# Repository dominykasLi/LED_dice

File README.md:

# LED_dice
Simple, random 6 sided dice generation electronics project.

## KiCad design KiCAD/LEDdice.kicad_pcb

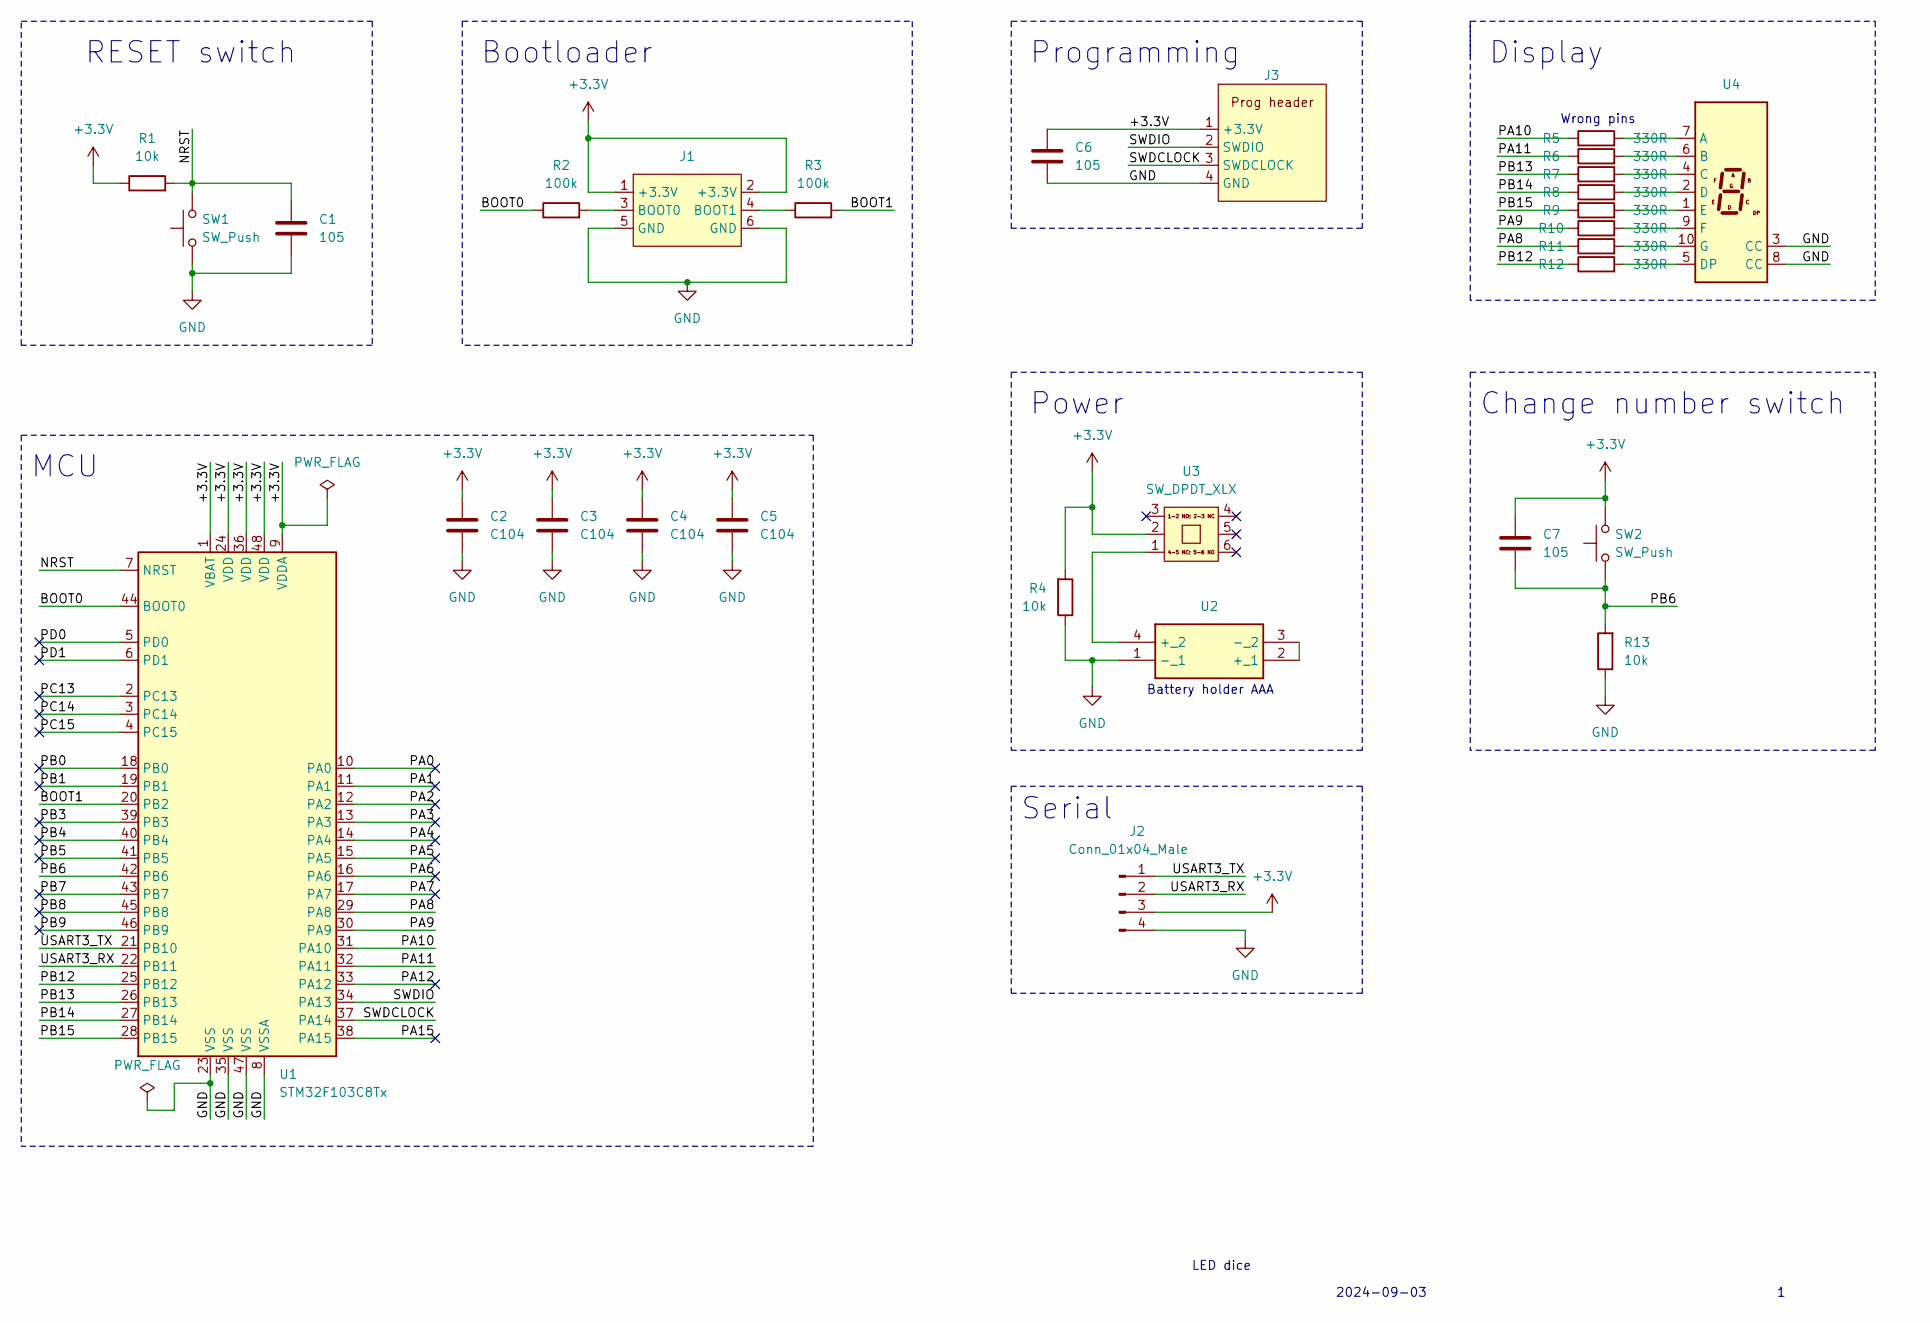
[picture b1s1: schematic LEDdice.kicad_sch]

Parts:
C1, C6, C7: 105; C_0805_2012Metric
C2, C3, C4, C5: C104; C_0805_2012Metric
J1: STM32_BOOT_Header_2x3; PinHeader_2x03_P2.54mm_Vertical
J2: Conn_01x04_Male; PinHeader_1x04_P2.54mm_Vertical
J3: STM32_Programming_Header_4; PinHeader_1x04_P2.54mm_Vertical
R1, R4, R13: 10k; R_0805_2012Metric
R2, R3: 100k; R_0805_2012Metric
R5, R6, R7, R8, R9, R10, R11, R12: 330R; R_0805_2012Metric
SW1: SW_Push; SW_Push_1P1T_NO_6x6mm_H9.5mm
SW2: SW_Push; SW_PUSH-12mm
U1: STM32F103C8Tx; LQFP-48_7x7mm_P0.5mm
U2: 1023; 2xAAA_Battery_Holder_SMD
U3: SW_DPDT_XLX
U4: 7_seg_5161AS_CC; 7_Seg_5161AS

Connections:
+3.3V: C2.1, C3.1, C4.1, C5.1, C6.1, C7.1, J1.1 (+3.3V), J1.2 (+3.3V), J2.3, J3.1 (+3.3V), R1.1, R4.2, SW2.2, U1.1 (VBAT), U1.9 (VDDA), U1.24 (VDD), U1.36 (VDD), U1.48 (VDD), U3.2; also elsewhere on the board
/BOOT0: R2.1, U1.44 (BOOT0)
/BOOT1: R3.2, U1.20 (PB2)
/NRST: C1.1, R1.2, SW1.2, U1.7 (NRST); also elsewhere on the board
/PA0: U1.10 (PA0)
/PA1: U1.11 (PA1)
/PA2: U1.12 (PA2)
/PA3: U1.13 (PA3)
/PA4: U1.14 (PA4)
/PA5: U1.15 (PA5)
/PA6: U1.16 (PA6)
/PA7: U1.17 (PA7)
/PA8: R11.1, U1.29 (PA8)
/PA9: R10.1, U1.30 (PA9)
/PA10: R5.1, U1.31 (PA10)
/PA11: R6.1, U1.32 (PA11)
/PA12: U1.33 (PA12)
/PA15: U1.38 (PA15)
/PB0: U1.18 (PB0)
/PB1: U1.19 (PB1)
/PB3: U1.39 (PB3)
/PB4: U1.40 (PB4)
/PB5: U1.41 (PB5)
/PB6: C7.2, R13.2, SW2.1, U1.42 (PB6); also elsewhere on the board
/PB7: U1.43 (PB7)
/PB8: U1.45 (PB8)
/PB9: U1.46 (PB9)
/PB12: R12.1, U1.25 (PB12)
/PB13: R7.1, U1.26 (PB13)
/PB14: R8.1, U1.27 (PB14)
/PB15: R9.1, U1.28 (PB15)
/PC13: U1.2 (PC13)
/PC14: U1.3 (PC14)
/PC15: U1.4 (PC15)
/PD0: U1.5 (PD0)
/PD1: U1.6 (PD1)
/SWDCLOCK: J3.3 (SWDCLOCK), U1.37 (PA14)
/SWDIO: J3.2 (SWDIO), U1.34 (PA13)
/USART3_RX: J2.2, U1.22 (PB11)
/USART3_TX: J2.1, U1.21 (PB10)
GND: C1.2, C2.2, C3.2, C4.2, C5.2, C6.2, J1.5 (GND), J1.6 (GND), J2.4, J3.4 (GND), R4.1, R13.1, SW1.1, U1.8 (VSSA), U1.23 (VSS), U1.35 (VSS), U1.47 (VSS), U2.1 (-_1), U4.3 (CC), U4.8 (CC); also elsewhere on the board
unnamed: J1.3 (BOOT0), R2.2
unnamed: J1.4 (BOOT1), R3.1
unnamed: R5.2, U4.7 (A)
unnamed: R6.2, U4.6 (B)
unnamed: R7.2, U4.4 (C)
unnamed: R8.2, U4.2 (D)
unnamed: R9.2, U4.1 (E)
unnamed: R10.2, U4.9 (F)
unnamed: R11.2, U4.10 (G)
unnamed: R12.2, U4.5 (DP)
unnamed: U2.2 (+_1), U2.3 (-_2)
unnamed: U2.4 (+_2), U3.1

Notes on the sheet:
Bootloader
Programming
RESET switch
Display
LED dice
Serial
MCU
2024-09-03
Change number switch
Wrong pins
Battery holder AAA
Power

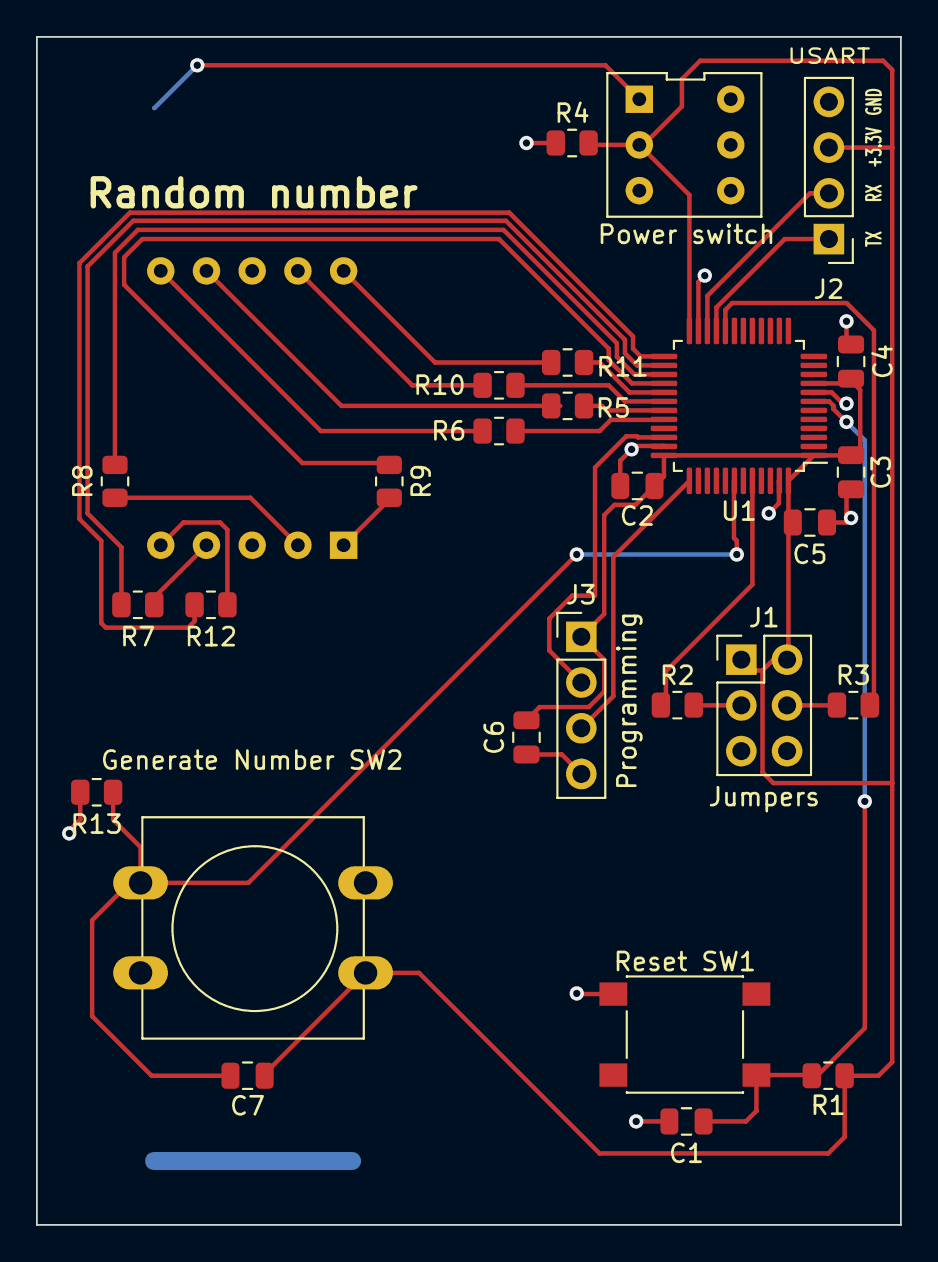
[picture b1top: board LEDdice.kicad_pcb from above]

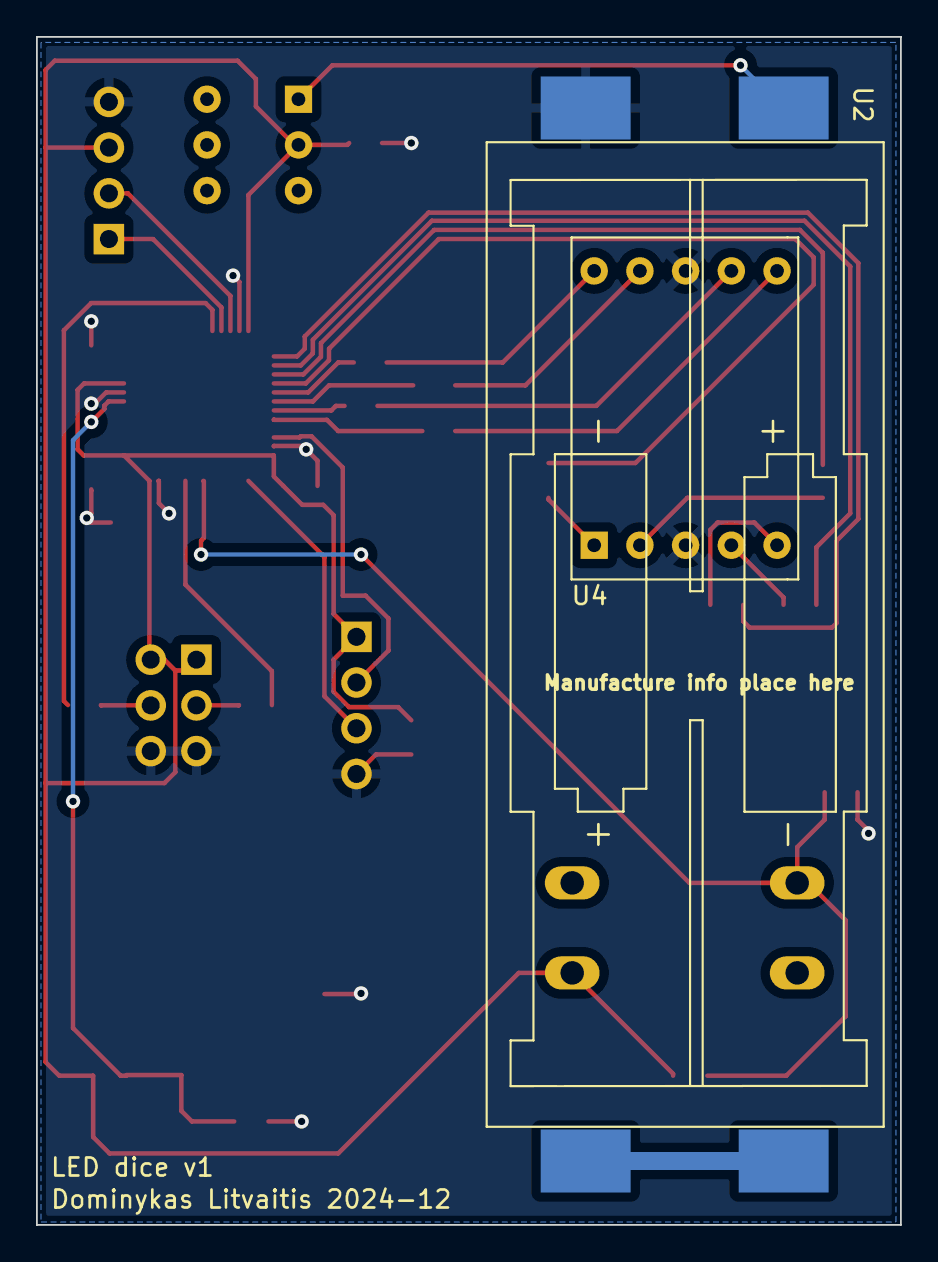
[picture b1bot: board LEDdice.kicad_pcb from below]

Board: 2 copper layers, 48.0 x 66.0 mm, 29 parts (2 on the bottom side), 30 nets.

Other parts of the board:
Generate Number SW2: SW_Push; SW_PUSH-12mm
Reset SW1: SW_Push; SW_Push_1P1T_NO_6x6mm_H9.5mm

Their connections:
+3.3V: Generate Number SW2.2; also elsewhere on the board
/NRST: Reset SW1.2; also elsewhere on the board
/PB6: Generate Number SW2.1; also elsewhere on the board
GND: Reset SW1.1; also elsewhere on the board

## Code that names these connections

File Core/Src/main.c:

/* USER CODE BEGIN Header */
/**
  ******************************************************************************
  * @file           : main.c
  * @brief          : Main program body
  ******************************************************************************
  * @attention
  *
  * Copyright (c) 2024 STMicroelectronics.
  * All rights reserved.
  *
  * This software is licensed under terms that can be found in the LICENSE file
  * in the root directory of this software component.
  * If no LICENSE file comes with this software, it is provided AS-IS.
  *
  ******************************************************************************
  */
/* USER CODE END Header */
/* Includes ------------------------------------------------------------------*/
#include "main.h"

/* Private includes ----------------------------------------------------------*/
/* USER CODE BEGIN Includes */
#include <time.h>
#include <stdlib.h>
#include <7seg.h>
/* USER CODE END Includes */

/* Private typedef -----------------------------------------------------------*/
/* USER CODE BEGIN PTD */

/* USER CODE END PTD */

/* Private define ------------------------------------------------------------*/
/* USER CODE BEGIN PD */

/* USER CODE END PD */

/* Private macro -------------------------------------------------------------*/
/* USER CODE BEGIN PM */

/* USER CODE END PM */

/* Private variables ---------------------------------------------------------*/
ADC_HandleTypeDef hadc1;

/* USER CODE BEGIN PV */

/* USER CODE END PV */

/* Private function prototypes -----------------------------------------------*/
void SystemClock_Config(void);
static void MX_GPIO_Init(void);
static void MX_ADC1_Init(void);
/* USER CODE BEGIN PFP */
void SystemClock_Config(void);
static void MX_GPIO_Init(void);
/* USER CODE END PFP */

/* Private user code ---------------------------------------------------------*/
/* USER CODE BEGIN 0 */

/* USER CODE END 0 */

/**
  * @brief  The application entry point.
  * @retval int
  */
int main(void)
{

  /* USER CODE BEGIN 1 */
  /* Random number to be generated between 1-6*/
  int Random_Number = 0;
  /* ADC raw values for rand() seed*/
  int raw = 0;
  /* USER CODE END 1 */

  /* MCU Configuration--------------------------------------------------------*/

  /* Reset of all peripherals, Initializes the Flash interface and the Systick. */
  HAL_Init();

  /* USER CODE BEGIN Init */

  /* USER CODE END Init */

  /* Configure the system clock */
  SystemClock_Config();

  /* USER CODE BEGIN SysInit */

  /* USER CODE END SysInit */

  /* Initialize all configured peripherals */
  MX_GPIO_Init();
  MX_ADC1_Init();
  /* USER CODE BEGIN 2 */

  /*This piece of code reads a tri-state pin and sets a random seed*/
  HAL_ADC_Start(&hadc1);
  HAL_ADC_PollForConversion(&hadc1, HAL_MAX_DELAY);
  raw = HAL_ADC_GetValue(&hadc1);
  srand(raw);
  /* USER CODE END 2 */

  /* Infinite loop */
  /* USER CODE BEGIN WHILE */
  while (1)
  {
    /* USER CODE END WHILE */

    /* USER CODE BEGIN 3 */

    // IF Button Is Pressed, get a random value
      if(HAL_GPIO_ReadPin(GPIOB, GPIO_PIN_6))
      {
          Clear_Display_Animation();
          /* random int between 1 and 6 */
          Random_Number = (rand() % 6) + 1;
          Display_Number(Random_Number);
          HAL_GPIO_WritePin(GPIOC, GPIO_PIN_13, GPIO_PIN_RESET);
          HAL_Delay(500);
      }
      else
      {
          // Else .. Turn LED OFF!
          // HAL_GPIO_WritePin(GPIOB, GPIO_PIN_15, GPIO_PIN_RESET);
      }
      
  }
  /* USER CODE END 3 */
}

/**
  * @brief System Clock Configuration
  * @retval None
  */
void SystemClock_Config(void)
{
  RCC_OscInitTypeDef RCC_OscInitStruct = {0};
  RCC_ClkInitTypeDef RCC_ClkInitStruct = {0};
  RCC_PeriphCLKInitTypeDef PeriphClkInit = {0};

  /** Initializes the RCC Oscillators according to the specified parameters
  * in the RCC_OscInitTypeDef structure.
  */
  RCC_OscInitStruct.OscillatorType = RCC_OSCILLATORTYPE_HSI;
  RCC_OscInitStruct.HSIState = RCC_HSI_ON;
  RCC_OscInitStruct.HSICalibrationValue = RCC_HSICALIBRATION_DEFAULT;
  RCC_OscInitStruct.PLL.PLLState = RCC_PLL_NONE;
  if (HAL_RCC_OscConfig(&RCC_OscInitStruct) != HAL_OK)
  {
    Error_Handler();
  }

  /** Initializes the CPU, AHB and APB buses clocks
  */
  RCC_ClkInitStruct.ClockType = RCC_CLOCKTYPE_HCLK|RCC_CLOCKTYPE_SYSCLK
                              |RCC_CLOCKTYPE_PCLK1|RCC_CLOCKTYPE_PCLK2;
  RCC_ClkInitStruct.SYSCLKSource = RCC_SYSCLKSOURCE_HSI;
  RCC_ClkInitStruct.AHBCLKDivider = RCC_SYSCLK_DIV1;
  RCC_ClkInitStruct.APB1CLKDivider = RCC_HCLK_DIV1;
  RCC_ClkInitStruct.APB2CLKDivider = RCC_HCLK_DIV1;

  if (HAL_RCC_ClockConfig(&RCC_ClkInitStruct, FLASH_LATENCY_0) != HAL_OK)
  {
    Error_Handler();
  }
  PeriphClkInit.PeriphClockSelection = RCC_PERIPHCLK_ADC;
  PeriphClkInit.AdcClockSelection = RCC_ADCPCLK2_DIV2;
  if (HAL_RCCEx_PeriphCLKConfig(&PeriphClkInit) != HAL_OK)
  {
    Error_Handler();
  }
}

/**
  * @brief ADC1 Initialization Function
  * @param None
  * @retval None
  */
static void MX_ADC1_Init(void)
{

  /* USER CODE BEGIN ADC1_Init 0 */

  /* USER CODE END ADC1_Init 0 */

  ADC_ChannelConfTypeDef sConfig = {0};

  /* USER CODE BEGIN ADC1_Init 1 */

  /* USER CODE END ADC1_Init 1 */

  /** Common config
  */
  hadc1.Instance = ADC1;
  hadc1.Init.ScanConvMode = ADC_SCAN_DISABLE;
  hadc1.Init.ContinuousConvMode = DISABLE;
  hadc1.Init.DiscontinuousConvMode = DISABLE;
  hadc1.Init.ExternalTrigConv = ADC_SOFTWARE_START;
  hadc1.Init.DataAlign = ADC_DATAALIGN_RIGHT;
  hadc1.Init.NbrOfConversion = 1;
  if (HAL_ADC_Init(&hadc1) != HAL_OK)
  {
    Error_Handler();
  }

  /** Configure Regular Channel
  */
  sConfig.Channel = ADC_CHANNEL_2;
  sConfig.Rank = ADC_REGULAR_RANK_1;
  sConfig.SamplingTime = ADC_SAMPLETIME_28CYCLES_5;
  if (HAL_ADC_ConfigChannel(&hadc1, &sConfig) != HAL_OK)
  {
    Error_Handler();
  }
  /* USER CODE BEGIN ADC1_Init 2 */

  /* USER CODE END ADC1_Init 2 */

}

/**
  * @brief GPIO Initialization Function
  * @param None
  * @retval None
  */
static void MX_GPIO_Init(void)
{
  GPIO_InitTypeDef GPIO_InitStruct = {0};
/* USER CODE BEGIN MX_GPIO_Init_1 */
/* USER CODE END MX_GPIO_Init_1 */

  /* GPIO Ports Clock Enable */
  __HAL_RCC_GPIOC_CLK_ENABLE();
  __HAL_RCC_GPIOA_CLK_ENABLE();
  __HAL_RCC_GPIOB_CLK_ENABLE();

  /*Configure GPIO pin Output Level */
  HAL_GPIO_WritePin(GPIOC, GPIO_PIN_13, GPIO_PIN_RESET);

  /*Configure GPIO pin Output Level */
  HAL_GPIO_WritePin(GPIOB, GPIO_PIN_12|GPIO_PIN_13|GPIO_PIN_14|GPIO_PIN_15, GPIO_PIN_RESET);

  /*Configure GPIO pin Output Level */
  HAL_GPIO_WritePin(GPIOA, GPIO_PIN_8|GPIO_PIN_9|GPIO_PIN_10|GPIO_PIN_11, GPIO_PIN_RESET);

  /*Configure GPIO pin : PC13 */
  GPIO_InitStruct.Pin = GPIO_PIN_13;
  GPIO_InitStruct.Mode = GPIO_MODE_OUTPUT_PP;
  GPIO_InitStruct.Pull = GPIO_NOPULL;
  GPIO_InitStruct.Speed = GPIO_SPEED_FREQ_LOW;
  HAL_GPIO_Init(GPIOC, &GPIO_InitStruct);

  /*Configure GPIO pins : PB12 PB13 PB14 PB15 */
  GPIO_InitStruct.Pin = GPIO_PIN_12|GPIO_PIN_13|GPIO_PIN_14|GPIO_PIN_15;
  GPIO_InitStruct.Mode = GPIO_MODE_OUTPUT_PP;
  GPIO_InitStruct.Pull = GPIO_NOPULL;
  GPIO_InitStruct.Speed = GPIO_SPEED_FREQ_LOW;
  HAL_GPIO_Init(GPIOB, &GPIO_InitStruct);

  /*Configure GPIO pins : PA8 PA9 PA10 PA11 */
  GPIO_InitStruct.Pin = GPIO_PIN_8|GPIO_PIN_9|GPIO_PIN_10|GPIO_PIN_11;
  GPIO_InitStruct.Mode = GPIO_MODE_OUTPUT_PP;
  GPIO_InitStruct.Pull = GPIO_NOPULL;
  GPIO_InitStruct.Speed = GPIO_SPEED_FREQ_LOW;
  HAL_GPIO_Init(GPIOA, &GPIO_InitStruct);

  /*Configure GPIO pin : PA12 */
  GPIO_InitStruct.Pin = GPIO_PIN_12;
  GPIO_InitStruct.Mode = GPIO_MODE_INPUT;
  GPIO_InitStruct.Pull = GPIO_NOPULL;
  HAL_GPIO_Init(GPIOA, &GPIO_InitStruct);

/* USER CODE BEGIN MX_GPIO_Init_2 */
/*Configure GPIO pin : PB6 */
  GPIO_InitStruct.Pin = GPIO_PIN_6;
  GPIO_InitStruct.Mode = GPIO_MODE_INPUT;
  GPIO_InitStruct.Pull = GPIO_PULLDOWN;
  HAL_GPIO_Init(GPIOB, &GPIO_InitStruct);
/* USER CODE END MX_GPIO_Init_2 */
}

/* USER CODE BEGIN 4 */

/* USER CODE END 4 */

/**
  * @brief  This function is executed in case of error occurrence.
  * @retval None
  */
void Error_Handler(void)
{
  /* USER CODE BEGIN Error_Handler_Debug */
  /* User can add his own implementation to report the HAL error return state */
  __disable_irq();
  while (1)
  {
  }
  /* USER CODE END Error_Handler_Debug */
}

#ifdef  USE_FULL_ASSERT
/**
  * @brief  Reports the name of the source file and the source line number
  *         where the assert_param error has occurred.
  * @param  file: pointer to the source file name
  * @param  line: assert_param error line source number
  * @retval None
  */
void assert_failed(uint8_t *file, uint32_t line)
{
  /* USER CODE BEGIN 6 */
  /* User can add his own implementation to report the file name and line number,
     ex: printf("Wrong parameters value: file %s on line %d\r\n", file, line) */
  /* USER CODE END 6 */
}
#endif /* USE_FULL_ASSERT */

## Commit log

2025-02-01 Uploading working project
2025-02-01 Uploading PCB V1 files
2025-02-01 PCB and schematic pdf
2025-02-01 Added photo
2025-02-13 Rename LEDdice__Assembly.pdf to LEDdice__Assembly_V1.pdf
    It is for version 1
2025-02-13 Rename schematic.pdf to schematic V1.pdf
